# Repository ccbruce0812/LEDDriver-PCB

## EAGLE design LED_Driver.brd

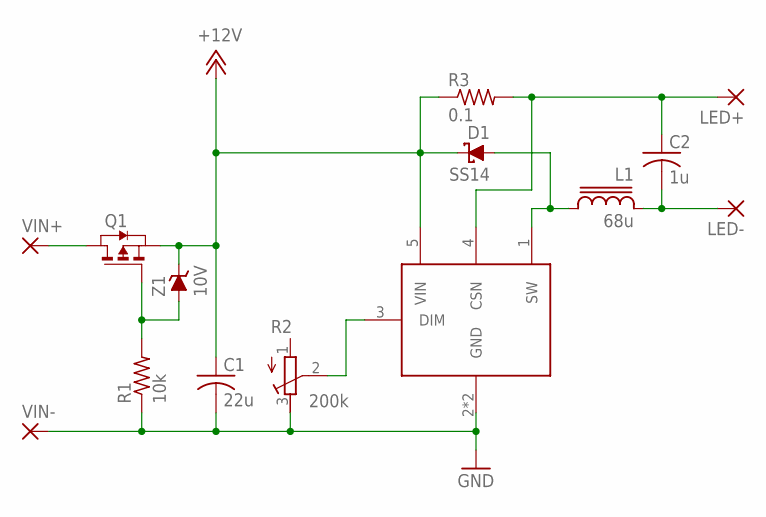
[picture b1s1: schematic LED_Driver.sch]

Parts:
C1: 22u; C1210K
C2: 1u; C0805K
D1: SS14; DO214AC
IC1: PT4115; SOT-89-5
L1: 68u; CDRH127/LD
LED+: SMD2; SMD1,27-2,54
LED-: SMD2; SMD1,27-2,54
Q1: PMOSSOT23; SOT-23
R1: 10k; R0805
R2: 200k; RTRIM3296W
R3: 0.1; R2512
VIN+: SMD2; SMD1,27-2,54
VIN-: SMD2; SMD1,27-2,54
Z1: 10V; SOD123

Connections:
+12V: C1.1, D1.C, IC1.5 (VIN), Q1.2 (S), R3.1, Z1.C
DIM: IC1.3 (DIM), R2.2 (S)
GND: C1.2, IC1.2 (GND), IC1.EX (GND), R1.1, R2.3 (E), VIN-.1
unnamed: C2.1, IC1.4 (CSN), LED+.1, R3.2
unnamed: D1.A, IC1.1 (SW), L1.2
unnamed: Q1.1 (D), VIN+.1
unnamed: C2.2, L1.1, LED-.1
unnamed: Q1.3 (G), R1.2, Z1.A

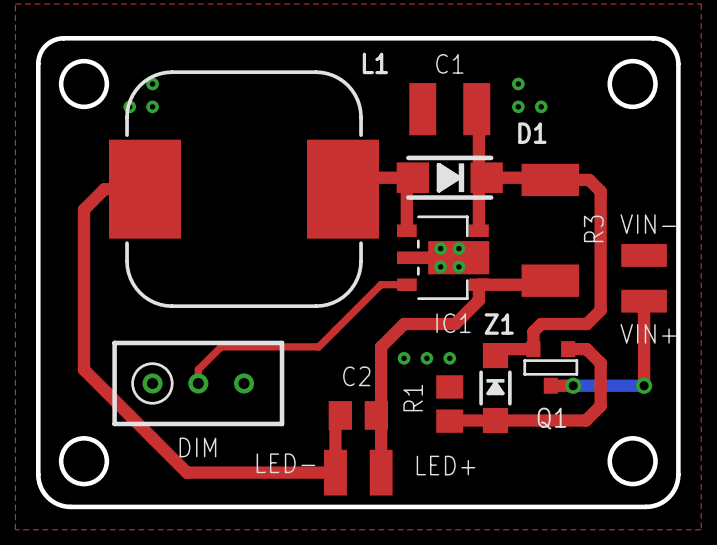
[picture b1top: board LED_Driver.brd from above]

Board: 2 copper layers, 35.6 x 26.0 mm, 14 parts (0 on the bottom side), 8 nets.

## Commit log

2018-06-24 Draft version.
